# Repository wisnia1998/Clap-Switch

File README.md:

# Clap-Switch
Clap-Switch - moje wykonanie przełącznika, reaguyjącego na pojedyńcze klaśnięcie, pstryknięcie, pozwala na sterowanie (załączanie i wyłączanie) urządzenia podpiętego do złącz przekaźnika.

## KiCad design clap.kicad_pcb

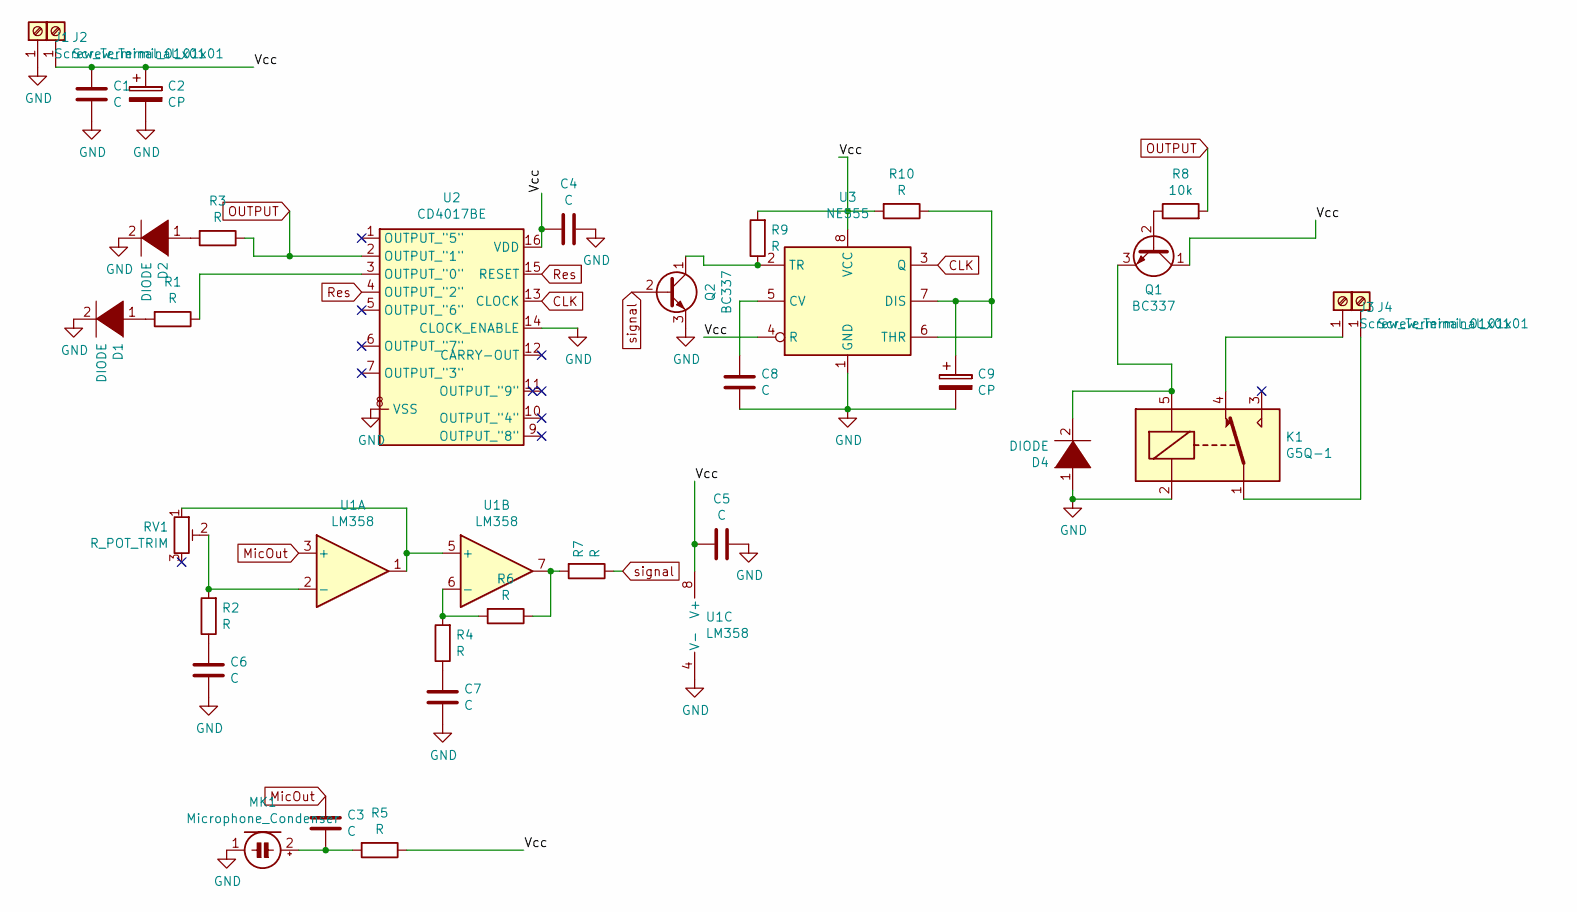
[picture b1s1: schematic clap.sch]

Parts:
C1, C3, C4, C5, C6, C7, C8: C; C_0805_2012Metric_Pad1.15x1.40mm_HandSolder
C2: CP; CP_Radial_D8.0mm_P2.50mm
C9: CP; CP_Radial_D6.3mm_P2.50mm
D1, D2, D4: DIODE; LED_D2.0mm_W4.0mm_H2.8mm_FlatTop
J1, J2, J3, J4: Screw_Terminal_01x01; SolderWirePad_1x01_Drill1.5mm
K1: G5Q-1; Relay_SPDT_SANYOU_SRD_Series_Form_C
MK1: Microphone_Condenser; LED_D2.0mm_W4.0mm_H2.8mm_FlatTop
Q1, Q2: BC337; TO-92_Inline
R1, R2, R3, R4, R5, R6, R7, R9, R10: R; R_0805_2012Metric_Pad1.15x1.40mm_HandSolder
R8: 10k; R_0805_2012Metric_Pad1.15x1.40mm_HandSolder
RV1: R_POT_TRIM; Potentiometer_Bourns_3296W_Vertical
U1: LM358; DIP-8_W7.62mm_LongPads
U2: CD4017BE; DIP-16_W10.16mm_LongPads
U3: NE555; DIP-8_W7.62mm_LongPads

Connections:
/Vcc: C1.1, C2.1, C4.2, C5.2, J2.1, Q1.1 (C), R5.1, R9.2, R10.2, U1.8 (V+), U2.16 (VDD), U3.4 (R), U3.8 (VCC)
CLK: U2.13 (CLOCK), U3.3 (Q)
GND: C1.2, C2.2, C4.1, C5.1, C6.1, C7.1, C8.1, C9.2, D1.2 (A), D2.2 (A), D4.1 (K), J1.1, K1.2, MK1.1 (-), Q2.3 (E), U1.4 (V-), U2.8 (VSS), U2.14 (CLOCK_ENABLE), U3.1 (GND)
MicOut: C3.2, U1.3 (+)
unnamed: C3.1, MK1.2 (+), R5.2
unnamed: C6.2, R2.1
unnamed: C7.2, R4.1
unnamed: C8.2, U3.5 (CV)
unnamed: C9.1, R10.1, U3.6 (THR), U3.7 (DIS)
unnamed: D1.1 (K), R1.2
unnamed: D2.1 (K), R3.2
unnamed: D4.2 (A), K1.5, Q1.3 (E)
unnamed: J3.1, K1.4
unnamed: J4.1, K1.1
unnamed: Q1.2 (B), R8.1
unnamed: Q2.1 (C), R9.1, U3.2 (TR)
unnamed: R1.1, U2.3 (OUTPUT_"0")
unnamed: R2.2, RV1.2, U1.2 (-)
unnamed: R4.2, R6.2, U1.6 (-)
unnamed: R6.1, R7.2, U1.7
unnamed: RV1.1, U1.1, U1.5 (+)
OUTPUT: R3.1, R8.2, U2.2 (OUTPUT_"1")
Res: U2.4 (OUTPUT_"2"), U2.15 (RESET)
signal: Q2.2 (B), R7.1

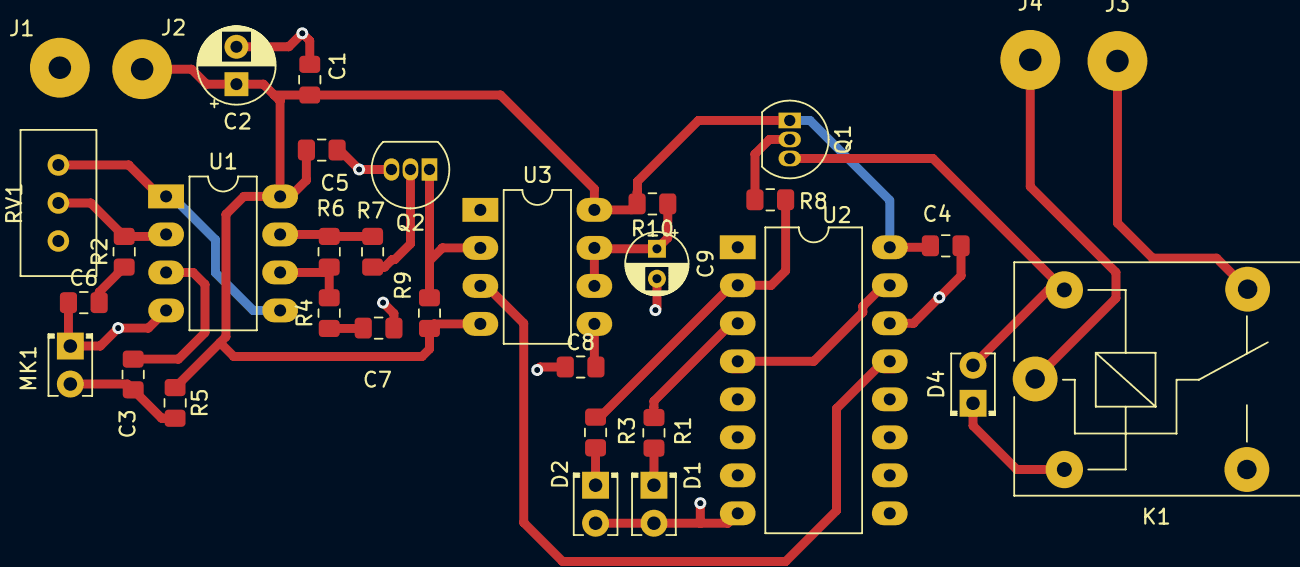
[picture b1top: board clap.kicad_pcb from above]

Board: 2 copper layers, 34 parts (0 on the bottom side), 24 nets.

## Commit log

2019-06-07 Create clap.kicad_pcb-bak
2020-10-13 refactoring
2020-10-13 add jpg
